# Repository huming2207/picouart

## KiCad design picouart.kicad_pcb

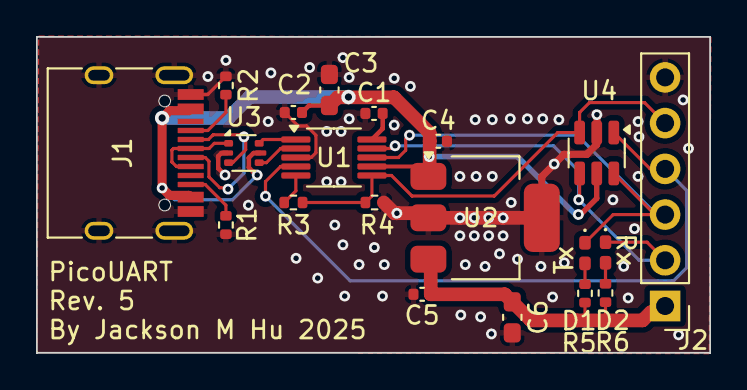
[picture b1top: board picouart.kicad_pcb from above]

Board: 2 copper layers, 37.4 x 17.5 mm, 20 parts (0 on the bottom side), 17 nets.

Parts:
C1, C2: 100nF; C_0402_1005Metric
C3, C6: 10uF; C_0603_1608Metric_Pad1.08x0.95mm_HandSolder
C4, C5: 0.1uF; C_0402_1005Metric
D1, D2: LED; LED_0402_1005Metric_Pad0.77x0.64mm_HandSolder
J1: USB; USB_C_Receptacle_HRO_TYPE-C-31-M-12
J2: UART; PinHeader_1x06_P2.54mm_Vertical
R1, R2: 5.11k; R_0402_1005Metric
R3, R4: 4.7k; R_0402_1005Metric
R5, R6: 1k; R_0402_1005Metric
U1: CH340X; MSOP-10_3x3mm_P0.5mm
U2: AP7361C-33E; SOT-223-3_TabPin2
U3: USBLC6-2P6; SOT-666
U4: USBLC6-4SC6; SOT-23-6

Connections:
+3V3: C5.1, C6.1, J2.1, R5.1, R6.1, U2.3 (VO)
+5V: C2.2, C3.1, C4.1, J1.A4 (VBUS), J1.A9 (VBUS), J1.B4 (VBUS), J1.B9 (VBUS), U1.7 (VCC), U2.1 (VI), U3.5 (VBUS), U4.5 (VBUS)
BOOT: J2.5, R3.2, R4.1, U1.6 (DTR), U4.3 (I/O2)
GND: C1.1, C2.1, C3.2, C4.2, C5.2, C6.2, J1.A1 (GND), J1.A12 (GND), J1.B1 (GND), J1.B12 (GND), J1.S1 (SHIELD), J2.6, R1.2, R2.2, R4.2, U1.3 (GND), U2.2 (GND), U3.2 (GND), U4.2 (GND)
unnamed: D1.2 (A), R5.2
unnamed: D2.2 (A), R6.2
unnamed: J1.A5 (CC1), R2.1
unnamed: J1.B5 (CC2), R1.1
unnamed: R3.1, U1.5 (CTS)
unnamed: C1.2, U1.10 (V3)
RESET: J2.4, U1.4 (RTS), U4.1 (I/O1)
RxD: D2.1 (K), J2.2, U1.9 (RXD), U4.4 (I/O3)
TxD: D1.1 (K), J2.3, U1.8 (TXD), U4.6 (I/O4)
USB_DM: U1.2 (DM), U3.4 (I/O2)
USB_DM_IN: J1.A7 (D-), J1.B7 (D-), U3.3 (I/O2)
USB_DP: U1.1 (DP), U3.6 (I/O1)
USB_DP_IN: J1.A6 (D+), J1.B6 (D+), U3.1 (I/O1)

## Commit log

2023-04-03 init
2023-04-03 Rev 3
2023-04-03 Ignore temp files
2023-04-03 Rev 3: make panel
2023-04-03 Sync submodule
2024-06-26 Work on Rev 4
2024-06-26 Ignore lockfile
2024-06-27 Rev 4
2025-01-24 Rev 5
